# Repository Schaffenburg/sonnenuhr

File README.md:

# sonnenuhr
UV radioation meter with a hardware analog clock display

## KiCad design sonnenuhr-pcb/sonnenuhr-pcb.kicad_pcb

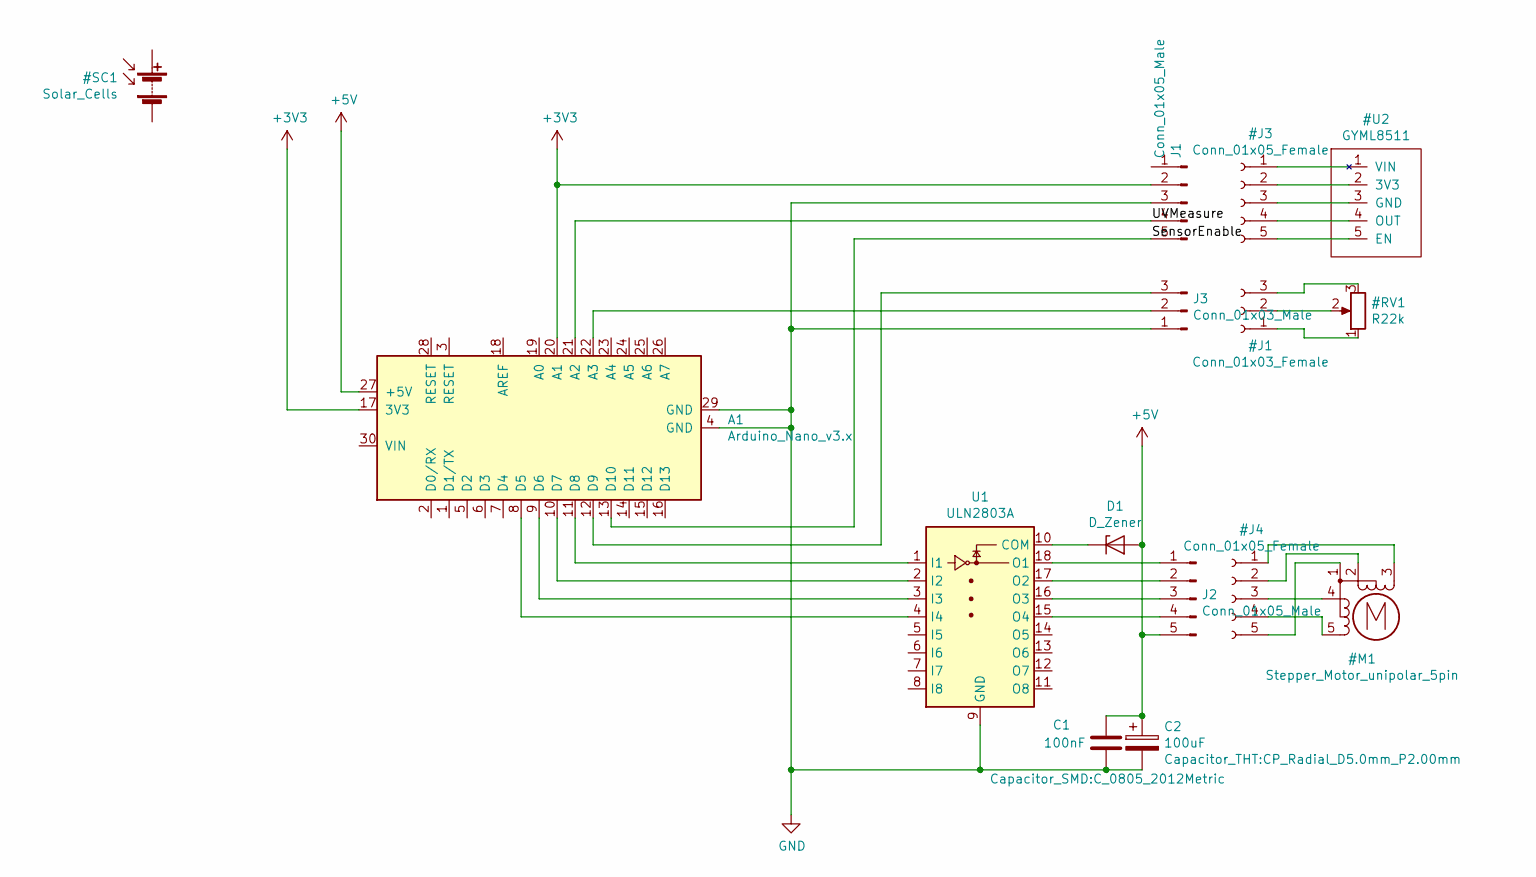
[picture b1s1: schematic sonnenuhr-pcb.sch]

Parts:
A1: Arduino_Nano_v3.x; Arduino_Nano
C1: 100nF; C_0805_2012Metric
C2: 100uF; CP_Radial_D5.0mm_P2.00mm
D1: D_Zener; D_T-1_P10.16mm_Horizontal
J1: Conn_01x05_Male; PinHeader_1x05_P2.54mm_Horizontal
J2: Conn_01x05_Male; JST_PH_B5B-PH-K_1x05_P2.00mm_Vertical
J3: Conn_01x03_Male; PinHeader_1x03_P2.54mm_Vertical
U1: ULN2803A; DIP-18_W7.62mm_Socket_LongPads

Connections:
+3V3: A1.17 (3V3), A1.20 (A1), J1.2
+5V: A1.27 (+5V), C1.1, C2.1, D1.2 (A), J2.5
/SensorEnable: A1.13 (D10), J1.5
/UVMeasure: A1.21 (A2), J1.4
GND: A1.4 (GND), A1.29 (GND), C1.2, C2.2, J1.3, J3.1, U1.9 (GND)
unnamed: A1.8 (D5), U1.4 (I4)
unnamed: A1.9 (D6), U1.3 (I3)
unnamed: A1.10 (D7), U1.2 (I2)
unnamed: A1.11 (D8), U1.1 (I1)
unnamed: A1.12 (D9), J3.3
unnamed: A1.22 (A3), J3.2
unnamed: D1.1 (K), U1.10 (COM)
unnamed: J2.1, U1.18 (O1)
unnamed: J2.2, U1.17 (O2)
unnamed: J2.3, U1.16 (O3)
unnamed: J2.4, U1.15 (O4)

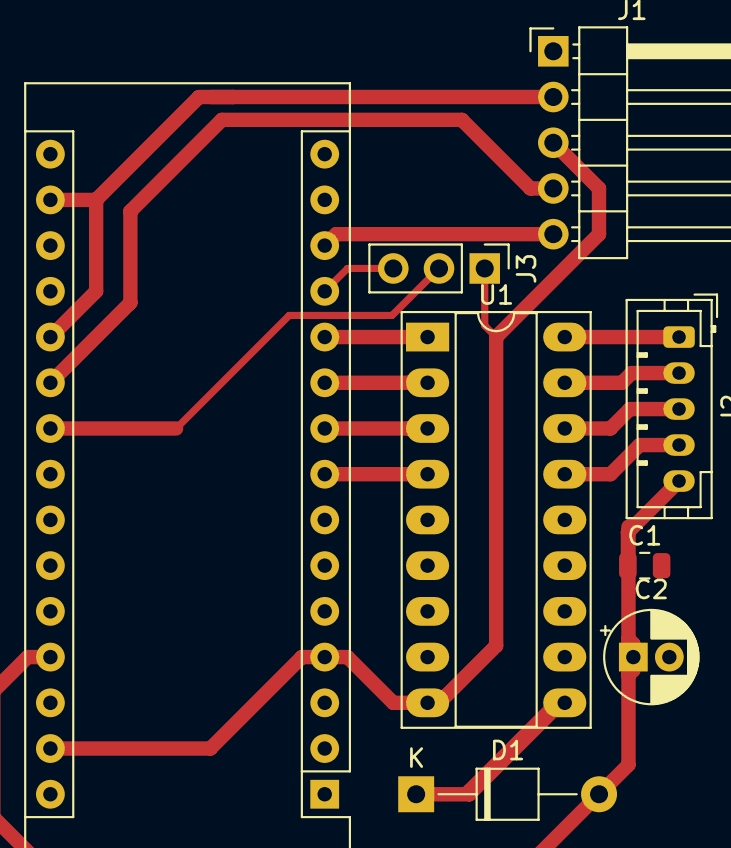
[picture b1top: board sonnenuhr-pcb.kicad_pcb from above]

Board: 2 copper layers, 8 parts (0 on the bottom side), 16 nets.

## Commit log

2019-05-05 Add sample code for reading from ML8511 UV sensor
2019-05-06 calculate UV Index
2019-05-06 send AVR into power safe and wake up on timer interrupt
2019-05-07 implement dummy stepper function
2019-05-25 Add bipolar stepper adjustment functionality
2019-05-25 4-hour position reset
2019-05-26 sonnenuhr-pcb: Add Kicad project for schematics and board
2019-05-28 Switch to Arduino NANOv3
2019-05-28 sonnenuhr-pcb: add capacitors
2019-05-28 Fix Reference Voltage for UV sensor
2019-05-28 implement Potentiometer for clock adjustment
2019-05-28 sonnenuhr-pcb: Add potentiometer
